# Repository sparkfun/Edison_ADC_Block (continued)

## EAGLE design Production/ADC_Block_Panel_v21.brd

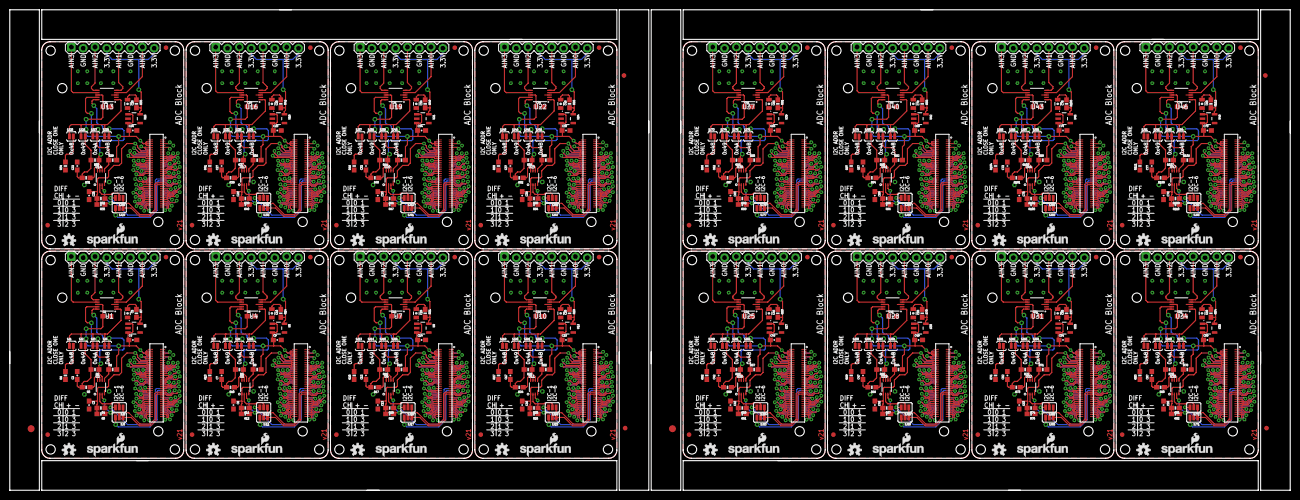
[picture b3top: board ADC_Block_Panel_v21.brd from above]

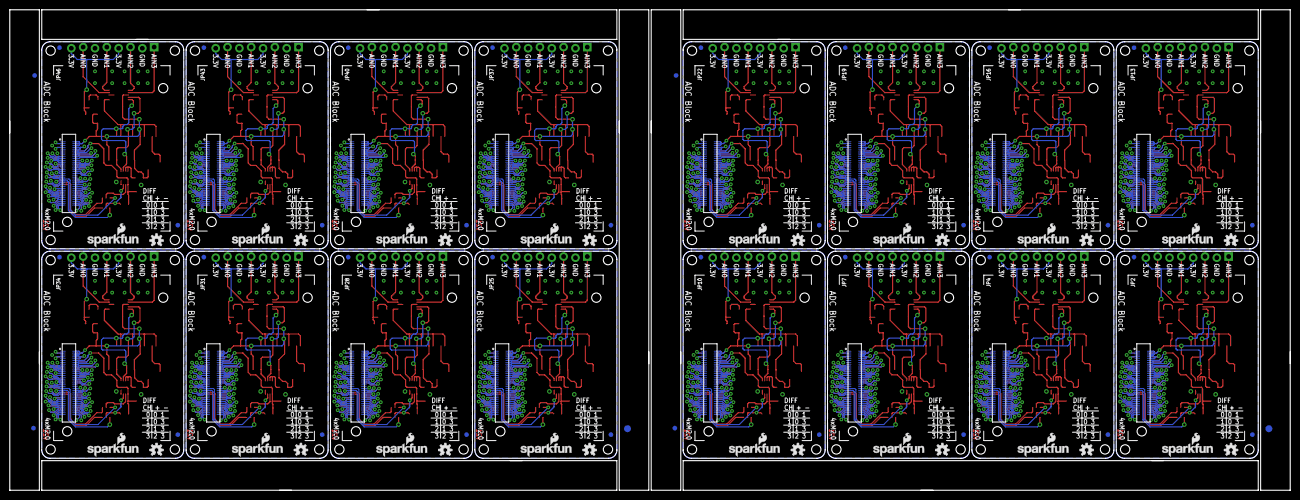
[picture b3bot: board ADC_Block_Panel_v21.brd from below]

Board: 2 copper layers, 274.8 x 103.1 mm, 524 parts (102 on the bottom side), 1136 nets.

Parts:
C1, C2, C3, C4, C6, C7, C8, C9, C11, C12, C13, C14, C16, C17, C18, C19, C21, C22, C23, C24, C26, C27, C28, C29, C31, C32, C33, C34, C36, C37, C38, C39, C41, C42, C43, C44, C46, C47, C48, C49, C51, C52, C53, C54, C56, C57, C58, C59, C61, C62, C63, C64, C66, C67, C68, C69, C71, C72, C73, C74, C76, C77, C78, C79: 0.1uF; 0603-CAP
C5, C10, C15, C20, C25, C30, C35, C40, C45, C50, C55, C60, C65, C70, C75, C80: 10uF; 0805-CAP
E$1, E$4, E$5, E$9: FIDUCIAL-1.5X3
E$2, E$3, E$6, E$7, E$8, E$10, E$11, E$12: FIDUCIAL-1X2
FID1, FID2, FID3, FID4, FID5, FID6, FID7, FID8, FID9, FID10, FID11, FID12, FID13, FID14, FID15, FID16, FID17, FID18, FID19, FID20, FID21, FID22, FID23, FID24, FID25, FID26, FID27, FID28, FID29, FID30, FID31, FID32, FID33, FID34, FID35, FID36, FID37, FID38, FID39, FID40, FID41, FID42, FID43, FID44, FID45, FID46, FID47, FID48, FID49, FID50, FID51, FID52, FID53, FID54, FID55, FID56, FID57, FID58, FID59, FID60, FID61, FID62, FID63, FID64: FIDUCIAL1X2; FIDUCIAL-1X2
JP1, JP6, JP9, JP12, JP15, JP18, JP21, JP24, JP27, JP30, JP33, JP36, JP39, JP42, JP45, JP48: 1X08_LOCK
JP2, JP4, JP7, JP10, JP13, JP16, JP19, JP22, JP25, JP28, JP31, JP34, JP37, JP40, JP43, JP46: EDISON_CONNECTOR_FULLMOUNTING_HOLES; EDISON_DAUGHTER
JP3, JP5, JP8, JP11, JP14, JP17, JP20, JP23, JP26, JP29, JP32, JP35, JP38, JP41, JP44, JP47: EDISON_CONNECTOR_FULLHEADER; DF40C-70DP-0.4(51)
LOGO1, LOGO3, LOGO6, LOGO7, LOGO10, LOGO11, LOGO14, LOGO15, LOGO18, LOGO19, LOGO22, LOGO23, LOGO26, LOGO27, LOGO30, LOGO31, LOGO34, LOGO35, LOGO38, LOGO39, LOGO42, LOGO43, LOGO46, LOGO47, LOGO50, LOGO51, LOGO54, LOGO55, LOGO58, LOGO59, LOGO62, LOGO63: SFE_LOGO_NAME_FLAME.1_INCH; SFE_LOGO_NAME_FLAME_.1
LOGO2, LOGO4, LOGO5, LOGO8, LOGO9, LOGO12, LOGO13, LOGO16, LOGO17, LOGO20, LOGO21, LOGO24, LOGO25, LOGO28, LOGO29, LOGO32, LOGO33, LOGO36, LOGO37, LOGO40, LOGO41, LOGO44, LOGO45, LOGO48, LOGO49, LOGO52, LOGO53, LOGO56, LOGO57, LOGO60, LOGO61, LOGO64: OSHW-LOGOS; OSHW-LOGO-S
R1, R2, R8, R9, R15, R16, R22, R23, R29, R30, R36, R37, R43, R44, R50, R51, R57, R58, R64, R65, R71, R72, R78, R79, R85, R86, R92, R93, R99, R100, R106, R107: 10K; 0603-RES
R3, R10, R17, R24, R31, R38, R45, R52, R59, R66, R73, R80, R87, R94, R101, R108: 200k; 0603-RES
R4, R5, R11, R12, R18, R19, R25, R26, R32, R33, R39, R40, R46, R47, R53, R54, R60, R61, R67, R68, R74, R75, R81, R82, R88, R89, R95, R96, R102, R103, R109, R110: DNP; 0603-RES
R6, R13, R20, R27, R34, R41, R48, R55, R62, R69, R76, R83, R90, R97, R104, R111: 2.2k; 0603-RES
R7, R14, R21, R28, R35, R42, R49, R56, R63, R70, R77, R84, R91, R98, R105, R112: 0.27; 0603-RES
SJ1, SJ7, SJ13, SJ19, SJ25, SJ31, SJ37, SJ43, SJ49, SJ55, SJ61, SJ67, SJ73, SJ79, SJ85, SJ91: JUMPER-PAD-2-NC_BY_PASTE; PAD-JUMPER-2-NC_BY_PASTE_YES_SILK
SJ2, SJ3, SJ4, SJ8, SJ9, SJ10, SJ14, SJ15, SJ16, SJ20, SJ21, SJ22, SJ26, SJ27, SJ28, SJ32, SJ33, SJ34, SJ38, SJ39, SJ40, SJ44, SJ45, SJ46, SJ50, SJ51, SJ52, SJ56, SJ57, SJ58, SJ62, SJ63, SJ64, SJ68, SJ69, SJ70, SJ74, SJ75, SJ76, SJ80, SJ81, SJ82, SJ86, SJ87, SJ88, SJ92, SJ93, SJ94: JUMPER-PAD-2-NOYES_SILK; PAD-JUMPER-2-NO_YES_SILK
SJ5, SJ11, SJ17, SJ23, SJ29, SJ35, SJ41, SJ47, SJ53, SJ59, SJ65, SJ71, SJ77, SJ83, SJ89, SJ95: SDA_SEL; PAD-JUMPER-3-2OF3_NC_BY_PASTE_YES_SILK_FULL_BOX
SJ6, SJ12, SJ18, SJ24, SJ30, SJ36, SJ42, SJ48, SJ54, SJ60, SJ66, SJ72, SJ78, SJ84, SJ90, SJ96: SCL_SEL; PAD-JUMPER-3-2OF3_NC_BY_PASTE_YES_SILK_FULL_BOX
U1, U4, U7, U10, U13, U16, U19, U22, U25, U28, U31, U34, U37, U40, U43, U46: ADS1015; MSOP10
U2, U5, U8, U11, U14, U17, U20, U23, U26, U29, U32, U35, U38, U41, U44, U47: PCA9306; PCA9306DC-1:1
U3, U6, U9, U12, U15, U18, U21, U24, U27, U30, U33, U36, U39, U42, U45, U48: 3.3V; SOT23-5

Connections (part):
1.8V: C3.1, JP2.12, JP3.12, R4.2, R5.2, U2.1
1.8V1: C8.1, JP4.12, JP5.12, R11.2, R12.2, U5.1
1.8V2: C13.1, JP7.12, JP8.12, R18.2, R19.2, U8.1
1.8V3: C18.1, JP10.12, JP11.12, R25.2, R26.2, U11.1
1.8V4: C23.1, JP13.12, JP14.12, R32.2, R33.2, U14.1
1.8V5: C28.1, JP16.12, JP17.12, R39.2, R40.2, U17.1
1.8V6: C33.1, JP19.12, JP20.12, R46.2, R47.2, U20.1
1.8V7: C38.1, JP22.12, JP23.12, R53.2, R54.2, U23.1
1.8V8: C43.1, JP25.12, JP26.12, R60.2, R61.2, U26.1
1.8V9: C48.1, JP28.12, JP29.12, R67.2, R68.2, U29.1
1.8V10: C53.1, JP31.12, JP32.12, R74.2, R75.2, U32.1
1.8V11: C58.1, JP34.12, JP35.12, R81.2, R82.2, U35.1
1.8V12: C63.1, JP37.12, JP38.12, R88.2, R89.2, U38.1
1.8V13: C68.1, JP40.12, JP41.12, R95.2, R96.2, U41.1
1.8V14: C73.1, JP43.12, JP44.12, R102.2, R103.2, U44.1
1.8V15: C78.1, JP46.12, JP47.12, R109.2, R110.2, U47.1
3.3V: JP2.8, JP2.10, JP3.8, JP3.10
3.3V1: JP4.8, JP4.10, JP5.8, JP5.10
3.3V2: JP7.8, JP7.10, JP8.8, JP8.10
3.3V3: JP10.8, JP10.10, JP11.8, JP11.10
3.3V4: JP13.8, JP13.10, JP14.8, JP14.10
3.3V5: JP16.8, JP16.10, JP17.8, JP17.10
3.3V6: JP19.8, JP19.10, JP20.8, JP20.10
3.3V7: JP22.8, JP22.10, JP23.8, JP23.10
3.3V8: JP25.8, JP25.10, JP26.8, JP26.10
3.3V9: JP28.8, JP28.10, JP29.8, JP29.10
3.3V10: JP31.8, JP31.10, JP32.8, JP32.10
3.3V11: JP34.8, JP34.10, JP35.8, JP35.10
3.3V12: JP37.8, JP37.10, JP38.8, JP38.10
3.3V13: JP40.8, JP40.10, JP41.8, JP41.10
3.3V14: JP43.8, JP43.10, JP44.8, JP44.10
3.3V15: JP46.8, JP46.10, JP47.8, JP47.10
A0+/AIN0: JP1.7, U1.4
A0+/AIN1: JP6.7, U4.4
A0+/AIN2: JP9.7, U7.4
A0+/AIN3: JP12.7, U10.4
A0+/AIN4: JP15.7, U13.4
A0+/AIN5: JP18.7, U16.4
A0+/AIN6: JP21.7, U19.4
A0+/AIN7: JP24.7, U22.4
A0+/AIN8: JP27.7, U25.4
A0+/AIN9: JP30.7, U28.4
A0+/AIN10: JP33.7, U31.4
A0+/AIN11: JP36.7, U34.4
A0+/AIN12: JP39.7, U37.4
A0+/AIN13: JP42.7, U40.4
A0+/AIN14: JP45.7, U43.4
A0+/AIN15: JP48.7, U46.4
A0-/AIN1: JP1.5, U1.5
A0-/AIN2: JP6.5, U4.5
A0-/AIN3: JP9.5, U7.5
A0-/AIN4: JP12.5, U10.5
A0-/AIN5: JP15.5, U13.5
A0-/AIN6: JP18.5, U16.5
A0-/AIN7: JP21.5, U19.5
A0-/AIN8: JP24.5, U22.5
A0-/AIN9: JP27.5, U25.5
A0-/AIN10: JP30.5, U28.5
A0-/AIN11: JP33.5, U31.5
A0-/AIN12: JP36.5, U34.5
A0-/AIN13: JP39.5, U37.5
A0-/AIN14: JP42.5, U40.5
A0-/AIN15: JP45.5, U43.5
A0-/AIN16: JP48.5, U46.5
A1+/AIN1: JP6.3, U4.6
A1+/AIN2: JP1.3, U1.6
A1+/AIN3: JP9.3, U7.6
A1+/AIN4: JP12.3, U10.6
A1+/AIN5: JP15.3, U13.6
A1+/AIN6: JP18.3, U16.6
A1+/AIN7: JP21.3, U19.6
A1+/AIN8: JP24.3, U22.6
A1+/AIN9: JP27.3, U25.6
A1+/AIN10: JP30.3, U28.6
A1+/AIN11: JP33.3, U31.6
A1+/AIN12: JP36.3, U34.6
A1+/AIN13: JP39.3, U37.6
A1+/AIN14: JP42.3, U40.6
A1+/AIN15: JP45.3, U43.6
A1+/AIN16: JP48.3, U46.6
A1-/AIN1: JP6.1, U4.7
A1-/AIN2: JP9.1, U7.7
A1-/AIN3: JP1.1, U1.7
A1-/AIN4: JP12.1, U10.7
A1-/AIN5: JP15.1, U13.7
A1-/AIN6: JP18.1, U16.7
A1-/AIN7: JP21.1, U19.7
A1-/AIN8: JP24.1, U22.7
A1-/AIN9: JP27.1, U25.7
A1-/AIN10: JP30.1, U28.7
A1-/AIN11: JP33.1, U31.7
A1-/AIN12: JP36.1, U34.7
A1-/AIN13: JP39.1, U37.7
A1-/AIN14: JP42.1, U40.7
A1-/AIN15: JP45.1, U43.7
A1-/AIN16: JP48.1, U46.7
ADDR: SJ1.1, SJ2.1, SJ3.1, SJ4.1, U1.1
ADDR1: SJ7.1, SJ8.1, SJ9.1, SJ10.1, U4.1
ADDR2: SJ13.1, SJ14.1, SJ15.1, SJ16.1, U7.1
ADDR3: SJ19.1, SJ20.1, SJ21.1, SJ22.1, U10.1
ADDR4: SJ25.1, SJ26.1, SJ27.1, SJ28.1, U13.1
ADDR5: SJ31.1, SJ32.1, SJ33.1, SJ34.1, U16.1
ADDR6: SJ37.1, SJ38.1, SJ39.1, SJ40.1, U19.1
ADDR7: SJ43.1, SJ44.1, SJ45.1, SJ46.1, U22.1
ADDR8: SJ49.1, SJ50.1, SJ51.1, SJ52.1, U25.1
ADDR9: SJ55.1, SJ56.1, SJ57.1, SJ58.1, U28.1
ADDR10: SJ61.1, SJ62.1, SJ63.1, SJ64.1, U31.1
ADDR11: SJ67.1, SJ68.1, SJ69.1, SJ70.1, U34.1
ADDR12: SJ73.1, SJ74.1, SJ75.1, SJ76.1, U37.1
ADDR13: SJ79.1, SJ80.1, SJ81.1, SJ82.1, U40.1
ADDR14: SJ85.1, SJ86.1, SJ87.1, SJ88.1, U43.1
ADDR15: SJ91.1, SJ92.1, SJ93.1, SJ94.1, U46.1
DCIN: JP2.14, JP3.14
DCIN1: JP4.14, JP5.14
DCIN2: JP7.14, JP8.14
DCIN3: JP10.14, JP11.14
DCIN4: JP13.14, JP14.14
DCIN5: JP16.14, JP17.14
DCIN6: JP19.14, JP20.14
DCIN7: JP22.14, JP23.14
DCIN8: JP25.14, JP26.14
DCIN9: JP28.14, JP29.14
DCIN10: JP31.14, JP32.14
DCIN11: JP34.14, JP35.14
DCIN12: JP37.14, JP38.14
DCIN13: JP40.14, JP41.14
DCIN14: JP43.14, JP44.14
DCIN15: JP46.14, JP47.14
FAULT: JP2.19, JP3.19
FAULT1: JP4.19, JP5.19
FAULT2: JP7.19, JP8.19
FAULT3: JP10.19, JP11.19
FAULT4: JP13.19, JP14.19
FAULT5: JP16.19, JP17.19
FAULT6: JP19.19, JP20.19
FAULT7: JP22.19, JP23.19
FAULT8: JP25.19, JP26.19
FAULT9: JP28.19, JP29.19
FAULT10: JP31.19, JP32.19
FAULT11: JP34.19, JP35.19
FAULT12: JP37.19, JP38.19
FAULT13: JP40.19, JP41.19
FAULT14: JP43.19, JP44.19
FAULT15: JP46.19, JP47.19
FW_RCVR: JP2.69, JP3.69
FW_RCVR1: JP4.69, JP5.69
FW_RCVR2: JP7.69, JP8.69
FW_RCVR3: JP10.69, JP11.69
FW_RCVR4: JP13.69, JP14.69
FW_RCVR5: JP16.69, JP17.69
FW_RCVR6: JP19.69, JP20.69
FW_RCVR7: JP22.69, JP23.69
FW_RCVR8: JP25.69, JP26.69
FW_RCVR9: JP28.69, JP29.69
FW_RCVR10: JP31.69, JP32.69
FW_RCVR11: JP34.69, JP35.69
FW_RCVR12: JP37.69, JP38.69
FW_RCVR13: JP40.69, JP41.69
FW_RCVR14: JP43.69, JP44.69
FW_RCVR15: JP46.69, JP47.69
GND: C1.2, C2.2, C3.2, C4.2, C5.2, JP1.2, JP1.6, JP2.1, JP2.5, JP2.9, JP2.11, JP2.13, JP2.15, JP3.1, JP3.5, JP3.9, JP3.11, JP3.13, JP3.15, R6.1, U1.3, U2.4, U3.2
GND1: C6.2, C7.2, C8.2, C9.2, C10.2, JP4.1, JP4.5, JP4.9, JP4.11, JP4.13, JP4.15, JP5.1, JP5.5, JP5.9, JP5.11, JP5.13, JP5.15, JP6.2, JP6.6, R13.1, U4.3, U5.4, U6.2
GND2: C11.2, C12.2, C13.2, C14.2, C15.2, JP7.1, JP7.5, JP7.9, JP7.11, JP7.13, JP7.15, JP8.1, JP8.5, JP8.9, JP8.11, JP8.13, JP8.15, JP9.2, JP9.6, R20.1, U7.3, U8.4, U9.2
GND3: C16.2, C17.2, C18.2, C19.2, C20.2, JP10.1, JP10.5, JP10.9, JP10.11, JP10.13, JP10.15, JP11.1, JP11.5, JP11.9, JP11.11, JP11.13, JP11.15, JP12.2, JP12.6, R27.1, U10.3, U11.4, U12.2
GND4: C21.2, C22.2, C23.2, C24.2, C25.2, JP13.1, JP13.5, JP13.9, JP13.11, JP13.13, JP13.15, JP14.1, JP14.5, JP14.9, JP14.11, JP14.13, JP14.15, JP15.2, JP15.6, R34.1, U13.3, U14.4, U15.2
GND5: C26.2, C27.2, C28.2, C29.2, C30.2, JP16.1, JP16.5, JP16.9, JP16.11, JP16.13, JP16.15, JP17.1, JP17.5, JP17.9, JP17.11, JP17.13, JP17.15, JP18.2, JP18.6, R41.1, U16.3, U17.4, U18.2
GND6: C31.2, C32.2, C33.2, C34.2, C35.2, JP19.1, JP19.5, JP19.9, JP19.11, JP19.13, JP19.15, JP20.1, JP20.5, JP20.9, JP20.11, JP20.13, JP20.15, JP21.2, JP21.6, R48.1, U19.3, U20.4, U21.2
GND7: C36.2, C37.2, C38.2, C39.2, C40.2, JP22.1, JP22.5, JP22.9, JP22.11, JP22.13, JP22.15, JP23.1, JP23.5, JP23.9, JP23.11, JP23.13, JP23.15, JP24.2, JP24.6, R55.1, U22.3, U23.4, U24.2
GND8: C41.2, C42.2, C43.2, C44.2, C45.2, JP25.1, JP25.5, JP25.9, JP25.11, JP25.13, JP25.15, JP26.1, JP26.5, JP26.9, JP26.11, JP26.13, JP26.15, JP27.2, JP27.6, R62.1, U25.3, U26.4, U27.2
GND9: C46.2, C47.2, C48.2, C49.2, C50.2, JP28.1, JP28.5, JP28.9, JP28.11, JP28.13, JP28.15, JP29.1, JP29.5, JP29.9, JP29.11, JP29.13, JP29.15, JP30.2, JP30.6, R69.1, U28.3, U29.4, U30.2
GND10: C51.2, C52.2, C53.2, C54.2, C55.2, JP31.1, JP31.5, JP31.9, JP31.11, JP31.13, JP31.15, JP32.1, JP32.5, JP32.9, JP32.11, JP32.13, JP32.15, JP33.2, JP33.6, R76.1, U31.3, U32.4, U33.2
GND11: C56.2, C57.2, C58.2, C59.2, C60.2, JP34.1, JP34.5, JP34.9, JP34.11, JP34.13, JP34.15, JP35.1, JP35.5, JP35.9, JP35.11, JP35.13, JP35.15, JP36.2, JP36.6, R83.1, U34.3, U35.4, U36.2
GND12: C61.2, C62.2, C63.2, C64.2, C65.2, JP37.1, JP37.5, JP37.9, JP37.11, JP37.13, JP37.15, JP38.1, JP38.5, JP38.9, JP38.11, JP38.13, JP38.15, JP39.2, JP39.6, R90.1, U37.3, U38.4, U39.2
GND13: C66.2, C67.2, C68.2, C69.2, C70.2, JP40.1, JP40.5, JP40.9, JP40.11, JP40.13, JP40.15, JP41.1, JP41.5, JP41.9, JP41.11, JP41.13, JP41.15, JP42.2, JP42.6, R97.1, U40.3, U41.4, U42.2
GND14: C71.2, C72.2, C73.2, C74.2, C75.2, JP43.1, JP43.5, JP43.9, JP43.11, JP43.13, JP43.15, JP44.1, JP44.5, JP44.9, JP44.11, JP44.13, JP44.15, JP45.2, JP45.6, R104.1, U43.3, U44.4, U45.2
GND15: C76.2, C77.2, C78.2, C79.2, C80.2, JP46.1, JP46.5, JP46.9, JP46.11, JP46.13, JP46.15, JP47.1, JP47.5, JP47.9, JP47.11, JP47.13, JP47.15, JP48.2, JP48.6, R111.1, U46.3, U47.4, U48.2
GP1: JP4.48, JP5.48
GP2: JP4.42, JP5.42
GP3: JP4.34, JP5.34
GP4: JP4.32, JP5.32
GP5: JP4.30, JP5.30
GP6: JP4.28, JP5.28
GP7: JP4.26, JP5.26
GP8: JP4.25, JP5.25
GP9: JP4.24, JP5.24
GP10: JP7.48, JP8.48
GP11: JP7.42, JP8.42
GP12: JP7.34, JP8.34
GP12_PWM0: JP2.35, JP3.35
GP12_PWM1: JP4.35, JP5.35
GP12_PWM2: JP7.35, JP8.35
GP12_PWM3: JP10.35, JP11.35
GP12_PWM4: JP13.35, JP14.35
GP12_PWM5: JP16.35, JP17.35
GP12_PWM6: JP19.35, JP20.35
GP12_PWM7: JP22.35, JP23.35
GP12_PWM8: JP25.35, JP26.35
GP12_PWM9: JP28.35, JP29.35
GP12_PWM10: JP31.35, JP32.35
GP12_PWM11: JP34.35, JP35.35
GP12_PWM12: JP37.35, JP38.35
GP12_PWM13: JP40.35, JP41.35
GP12_PWM14: JP43.35, JP44.35
GP12_PWM15: JP46.35, JP47.35
GP13: JP7.32, JP8.32
GP13_PWM1: JP2.33, JP3.33
GP13_PWM2: JP4.33, JP5.33
GP13_PWM3: JP7.33, JP8.33
GP13_PWM4: JP10.33, JP11.33
GP13_PWM5: JP13.33, JP14.33
GP13_PWM6: JP16.33, JP17.33
GP13_PWM7: JP19.33, JP20.33
GP13_PWM8: JP22.33, JP23.33
GP13_PWM9: JP25.33, JP26.33
GP13_PWM10: JP28.33, JP29.33
GP13_PWM11: JP31.33, JP32.33
GP13_PWM12: JP34.33, JP35.33
GP13_PWM13: JP37.33, JP38.33
GP13_PWM14: JP40.33, JP41.33
GP13_PWM15: JP43.33, JP44.33
GP13_PWM16: JP46.33, JP47.33
GP14: JP2.48, JP3.48
GP15: JP2.42, JP3.42
GP16: JP7.30, JP8.30
GP17: JP7.28, JP8.28
GP18: JP7.26, JP8.26
GP19: JP7.25, JP8.25
GP19_I2C_1_SCL: JP2.41, JP3.41, SJ6.3
GP19_I2C_1_SCL1: JP4.41, JP5.41, SJ12.3
GP19_I2C_1_SCL2: JP7.41, JP8.41, SJ18.3
GP19_I2C_1_SCL3: JP10.41, JP11.41, SJ24.3
GP19_I2C_1_SCL4: JP13.41, JP14.41, SJ30.3
GP19_I2C_1_SCL5: JP16.41, JP17.41, SJ36.3
GP19_I2C_1_SCL6: JP19.41, JP20.41, SJ42.3
GP19_I2C_1_SCL7: JP22.41, JP23.41, SJ48.3
GP19_I2C_1_SCL8: JP25.41, JP26.41, SJ54.3
GP19_I2C_1_SCL9: JP28.41, JP29.41, SJ60.3
GP19_I2C_1_SCL10: JP31.41, JP32.41, SJ66.3
GP19_I2C_1_SCL11: JP34.41, JP35.41, SJ72.3
GP19_I2C_1_SCL12: JP37.41, JP38.41, SJ78.3
GP19_I2C_1_SCL13: JP40.41, JP41.41, SJ84.3
GP19_I2C_1_SCL14: JP43.41, JP44.41, SJ90.3
GP19_I2C_1_SCL15: JP46.41, JP47.41, SJ96.3
GP20: JP7.24, JP8.24
GP20_I2C_1_SDA: JP2.43, JP3.43, SJ5.3
GP20_I2C_1_SDA1: JP4.43, JP5.43, SJ11.3
GP20_I2C_1_SDA2: JP7.43, JP8.43, SJ17.3
GP20_I2C_1_SDA3: JP10.43, JP11.43, SJ23.3
GP20_I2C_1_SDA4: JP13.43, JP14.43, SJ29.3
GP20_I2C_1_SDA5: JP16.43, JP17.43, SJ35.3
GP20_I2C_1_SDA6: JP19.43, JP20.43, SJ41.3
GP20_I2C_1_SDA7: JP22.43, JP23.43, SJ47.3
GP20_I2C_1_SDA8: JP25.43, JP26.43, SJ53.3
GP20_I2C_1_SDA9: JP28.43, JP29.43, SJ59.3
GP20_I2C_1_SDA10: JP31.43, JP32.43, SJ65.3
GP20_I2C_1_SDA11: JP34.43, JP35.43, SJ71.3
GP20_I2C_1_SDA12: JP37.43, JP38.43, SJ77.3
GP20_I2C_1_SDA13: JP40.43, JP41.43, SJ83.3
GP20_I2C_1_SDA14: JP43.43, JP44.43, SJ89.3
GP20_I2C_1_SDA15: JP46.43, JP47.43, SJ95.3
GP21: JP10.48, JP11.48
GP22: JP10.42, JP11.42
GP23: JP10.34, JP11.34
GP24: JP10.32, JP11.32
GP25: JP10.30, JP11.30
GP26: JP10.28, JP11.28
GP27: JP10.26, JP11.26
GP27_I2C_6_SCL: JP2.45, JP3.45, SJ6.1
GP27_I2C_6_SCL1: JP4.45, JP5.45, SJ12.1
GP27_I2C_6_SCL2: JP7.45, JP8.45, SJ18.1
GP27_I2C_6_SCL3: JP10.45, JP11.45, SJ24.1
GP27_I2C_6_SCL4: JP13.45, JP14.45, SJ30.1
GP27_I2C_6_SCL5: JP16.45, JP17.45, SJ36.1
GP27_I2C_6_SCL6: JP19.45, JP20.45, SJ42.1
GP27_I2C_6_SCL7: JP22.45, JP23.45, SJ48.1
GP27_I2C_6_SCL8: JP25.45, JP26.45, SJ54.1
GP27_I2C_6_SCL9: JP28.45, JP29.45, SJ60.1
GP27_I2C_6_SCL10: JP31.45, JP32.45, SJ66.1
GP27_I2C_6_SCL11: JP34.45, JP35.45, SJ72.1
GP27_I2C_6_SCL12: JP37.45, JP38.45, SJ78.1
GP27_I2C_6_SCL13: JP40.45, JP41.45, SJ84.1
GP27_I2C_6_SCL14: JP43.45, JP44.45, SJ90.1
GP27_I2C_6_SCL15: JP46.45, JP47.45, SJ96.1
GP28: JP10.25, JP11.25
GP28_I2C_6_SDA: JP2.47, JP3.47, SJ5.1
GP28_I2C_6_SDA1: JP4.47, JP5.47, SJ11.1
GP28_I2C_6_SDA2: JP7.47, JP8.47, SJ17.1
GP28_I2C_6_SDA3: JP10.47, JP11.47, SJ23.1
GP28_I2C_6_SDA4: JP13.47, JP14.47, SJ29.1
GP28_I2C_6_SDA5: JP16.47, JP17.47, SJ35.1
GP28_I2C_6_SDA6: JP19.47, JP20.47, SJ41.1
GP28_I2C_6_SDA7: JP22.47, JP23.47, SJ47.1
GP28_I2C_6_SDA8: JP25.47, JP26.47, SJ53.1
GP28_I2C_6_SDA9: JP28.47, JP29.47, SJ59.1
GP28_I2C_6_SDA10: JP31.47, JP32.47, SJ65.1
GP28_I2C_6_SDA11: JP34.47, JP35.47, SJ71.1
GP28_I2C_6_SDA12: JP37.47, JP38.47, SJ77.1
GP28_I2C_6_SDA13: JP40.47, JP41.47, SJ83.1
GP28_I2C_6_SDA14: JP43.47, JP44.47, SJ89.1
GP28_I2C_6_SDA15: JP46.47, JP47.47, SJ95.1
GP29: JP10.24, JP11.24
GP30: JP13.48, JP14.48
GP31: JP13.42, JP14.42
GP32: JP13.34, JP14.34
GP33: JP13.32, JP14.32
GP34: JP13.30, JP14.30
GP35: JP13.28, JP14.28
GP36: JP13.26, JP14.26
GP37: JP13.25, JP14.25
GP38: JP13.24, JP14.24
GP39: JP16.48, JP17.48
GP40: JP16.42, JP17.42
GP40_I2S_2_CLK: JP2.52, JP3.52
GP40_I2S_2_CLK1: JP4.52, JP5.52
GP40_I2S_2_CLK2: JP7.52, JP8.52
GP40_I2S_2_CLK3: JP10.52, JP11.52
GP40_I2S_2_CLK4: JP13.52, JP14.52
GP40_I2S_2_CLK5: JP16.52, JP17.52
GP40_I2S_2_CLK6: JP19.52, JP20.52
GP40_I2S_2_CLK7: JP22.52, JP23.52
GP40_I2S_2_CLK8: JP25.52, JP26.52
GP40_I2S_2_CLK9: JP28.52, JP29.52
GP40_I2S_2_CLK10: JP31.52, JP32.52
GP40_I2S_2_CLK11: JP34.52, JP35.52
GP40_I2S_2_CLK12: JP37.52, JP38.52
GP40_I2S_2_CLK13: JP40.52, JP41.52
GP40_I2S_2_CLK14: JP43.52, JP44.52
GP40_I2S_2_CLK15: JP46.52, JP47.52
GP41: JP16.34, JP17.34
GP41_I2S_2_FS: JP2.54, JP3.54
GP41_I2S_2_FS1: JP4.54, JP5.54
GP41_I2S_2_FS2: JP7.54, JP8.54
GP41_I2S_2_FS3: JP10.54, JP11.54
GP41_I2S_2_FS4: JP13.54, JP14.54
GP41_I2S_2_FS5: JP16.54, JP17.54
GP41_I2S_2_FS6: JP19.54, JP20.54
GP41_I2S_2_FS7: JP22.54, JP23.54
GP41_I2S_2_FS8: JP25.54, JP26.54
GP41_I2S_2_FS9: JP28.54, JP29.54
GP41_I2S_2_FS10: JP31.54, JP32.54
GP41_I2S_2_FS11: JP34.54, JP35.54
GP41_I2S_2_FS12: JP37.54, JP38.54
GP41_I2S_2_FS13: JP40.54, JP41.54
GP41_I2S_2_FS14: JP43.54, JP44.54
GP41_I2S_2_FS15: JP46.54, JP47.54
GP42: JP16.32, JP17.32
GP42_I2S_2_RXD: JP2.50, JP3.50
GP42_I2S_2_RXD1: JP4.50, JP5.50
GP42_I2S_2_RXD2: JP7.50, JP8.50
GP42_I2S_2_RXD3: JP10.50, JP11.50
GP42_I2S_2_RXD4: JP13.50, JP14.50
GP42_I2S_2_RXD5: JP16.50, JP17.50
GP42_I2S_2_RXD6: JP19.50, JP20.50
GP42_I2S_2_RXD7: JP22.50, JP23.50
GP42_I2S_2_RXD8: JP25.50, JP26.50
GP42_I2S_2_RXD9: JP28.50, JP29.50
GP42_I2S_2_RXD10: JP31.50, JP32.50
GP42_I2S_2_RXD11: JP34.50, JP35.50
GP42_I2S_2_RXD12: JP37.50, JP38.50
GP42_I2S_2_RXD13: JP40.50, JP41.50
GP42_I2S_2_RXD14: JP43.50, JP44.50
GP42_I2S_2_RXD15: JP46.50, JP47.50
GP43: JP16.30, JP17.30
GP43_I2S_2_TXD: JP2.56, JP3.56
GP43_I2S_2_TXD1: JP4.56, JP5.56
GP43_I2S_2_TXD2: JP7.56, JP8.56
GP43_I2S_2_TXD3: JP10.56, JP11.56
GP43_I2S_2_TXD4: JP13.56, JP14.56
GP43_I2S_2_TXD5: JP16.56, JP17.56
GP43_I2S_2_TXD6: JP19.56, JP20.56
GP43_I2S_2_TXD7: JP22.56, JP23.56
GP43_I2S_2_TXD8: JP25.56, JP26.56
GP43_I2S_2_TXD9: JP28.56, JP29.56
GP43_I2S_2_TXD10: JP31.56, JP32.56
GP43_I2S_2_TXD11: JP34.56, JP35.56
GP43_I2S_2_TXD12: JP37.56, JP38.56
GP43_I2S_2_TXD13: JP40.56, JP41.56
GP43_I2S_2_TXD14: JP43.56, JP44.56
GP43_I2S_2_TXD15: JP46.56, JP47.56
GP44: JP2.24, JP3.24
GP45: JP2.26, JP3.26
GP46: JP2.28, JP3.28
GP47: JP2.30, JP3.30
GP48: JP2.32, JP3.32
GP49: JP2.34, JP3.34
GP50: JP16.28, JP17.28
GP51: JP16.26, JP17.26
GP52: JP16.25, JP17.25
GP53: JP16.24, JP17.24
GP54: JP19.48, JP20.48
GP55: JP19.42, JP20.42
GP56: JP19.34, JP20.34
GP57: JP19.32, JP20.32
GP58: JP19.30, JP20.30
GP59: JP19.28, JP20.28
GP60: JP19.26, JP20.26
GP61: JP19.25, JP20.25
GP62: JP19.24, JP20.24
GP63: JP22.48, JP23.48
GP64: JP22.42, JP23.42
GP65: JP22.34, JP23.34
GP66: JP22.32, JP23.32
GP67: JP22.30, JP23.30
GP68: JP22.28, JP23.28
GP69: JP22.26, JP23.26
GP70: JP22.25, JP23.25
GP71: JP22.24, JP23.24
GP72: JP25.48, JP26.48
GP73: JP25.42, JP26.42
GP74: JP25.34, JP26.34
GP75: JP25.32, JP26.32
GP76: JP25.30, JP26.30
GP77: JP25.28, JP26.28
GP77_SD_0_CD#: JP2.60, JP3.60
GP77_SD_0_CD#1: JP4.60, JP5.60
GP77_SD_0_CD#2: JP7.60, JP8.60
GP77_SD_0_CD#3: JP10.60, JP11.60
GP77_SD_0_CD#4: JP13.60, JP14.60
GP77_SD_0_CD#5: JP16.60, JP17.60
GP77_SD_0_CD#6: JP19.60, JP20.60
GP77_SD_0_CD#7: JP22.60, JP23.60
GP77_SD_0_CD#8: JP25.60, JP26.60
GP77_SD_0_CD#9: JP28.60, JP29.60
GP77_SD_0_CD#10: JP31.60, JP32.60
GP77_SD_0_CD#11: JP34.60, JP35.60
GP77_SD_0_CD#12: JP37.60, JP38.60
GP77_SD_0_CD#13: JP40.60, JP41.60
GP77_SD_0_CD#14: JP43.60, JP44.60
GP77_SD_0_CD#15: JP46.60, JP47.60
GP78: JP25.26, JP26.26
GP78_SD_0_CLK: JP2.58, JP3.58
GP78_SD_0_CLK1: JP4.58, JP5.58
GP78_SD_0_CLK2: JP7.58, JP8.58
GP78_SD_0_CLK3: JP10.58, JP11.58
GP78_SD_0_CLK4: JP13.58, JP14.58
GP78_SD_0_CLK5: JP16.58, JP17.58
GP78_SD_0_CLK6: JP19.58, JP20.58
GP78_SD_0_CLK7: JP22.58, JP23.58
GP78_SD_0_CLK8: JP25.58, JP26.58
GP78_SD_0_CLK9: JP28.58, JP29.58
GP78_SD_0_CLK10: JP31.58, JP32.58
GP78_SD_0_CLK11: JP34.58, JP35.58
GP78_SD_0_CLK12: JP37.58, JP38.58
GP78_SD_0_CLK13: JP40.58, JP41.58
GP78_SD_0_CLK14: JP43.58, JP44.58
GP78_SD_0_CLK15: JP46.58, JP47.58
GP79: JP25.25, JP26.25
GP79_SD_0_CMD: JP2.62, JP3.62
GP79_SD_0_CMD1: JP4.62, JP5.62
GP79_SD_0_CMD2: JP7.62, JP8.62
GP79_SD_0_CMD3: JP10.62, JP11.62
GP79_SD_0_CMD4: JP13.62, JP14.62
GP79_SD_0_CMD5: JP16.62, JP17.62
GP79_SD_0_CMD6: JP19.62, JP20.62
GP79_SD_0_CMD7: JP22.62, JP23.62
GP79_SD_0_CMD8: JP25.62, JP26.62
GP79_SD_0_CMD9: JP28.62, JP29.62
GP79_SD_0_CMD10: JP31.62, JP32.62
GP79_SD_0_CMD11: JP34.62, JP35.62
GP79_SD_0_CMD12: JP37.62, JP38.62
GP79_SD_0_CMD13: JP40.62, JP41.62
GP79_SD_0_CMD14: JP43.62, JP44.62
GP79_SD_0_CMD15: JP46.62, JP47.62
GP80: JP25.24, JP26.24
GP80_SD_0_DAT0: JP2.66, JP3.66
GP80_SD_0_DAT1: JP4.66, JP5.66
GP80_SD_0_DAT2: JP7.66, JP8.66
GP80_SD_0_DAT3: JP10.66, JP11.66
GP80_SD_0_DAT4: JP13.66, JP14.66
GP80_SD_0_DAT5: JP16.66, JP17.66
GP80_SD_0_DAT6: JP19.66, JP20.66
GP80_SD_0_DAT7: JP22.66, JP23.66
GP80_SD_0_DAT8: JP25.66, JP26.66
GP80_SD_0_DAT9: JP28.66, JP29.66
GP80_SD_0_DAT10: JP31.66, JP32.66
GP80_SD_0_DAT11: JP34.66, JP35.66
GP80_SD_0_DAT12: JP37.66, JP38.66
GP80_SD_0_DAT13: JP40.66, JP41.66
GP80_SD_0_DAT14: JP43.66, JP44.66
GP80_SD_0_DAT15: JP46.66, JP47.66
GP81: JP28.48, JP29.48
GP81_SD_0_DAT1: JP2.70, JP3.70
GP81_SD_0_DAT2: JP4.70, JP5.70
GP81_SD_0_DAT3: JP7.70, JP8.70
GP81_SD_0_DAT4: JP10.70, JP11.70
GP81_SD_0_DAT5: JP13.70, JP14.70
GP81_SD_0_DAT6: JP16.70, JP17.70
GP81_SD_0_DAT7: JP19.70, JP20.70
GP81_SD_0_DAT8: JP22.70, JP23.70
GP81_SD_0_DAT9: JP25.70, JP26.70
GP81_SD_0_DAT10: JP28.70, JP29.70
GP81_SD_0_DAT11: JP31.70, JP32.70
GP81_SD_0_DAT12: JP34.70, JP35.70
GP81_SD_0_DAT13: JP37.70, JP38.70
GP81_SD_0_DAT14: JP40.70, JP41.70
GP81_SD_0_DAT15: JP43.70, JP44.70
GP81_SD_0_DAT16: JP46.70, JP47.70
GP82: JP28.42, JP29.42
GP82_SD_0_DAT1: JP4.64, JP5.64
GP82_SD_0_DAT2: JP2.64, JP3.64
GP82_SD_0_DAT3: JP7.64, JP8.64
GP82_SD_0_DAT4: JP10.64, JP11.64
GP82_SD_0_DAT5: JP13.64, JP14.64
GP82_SD_0_DAT6: JP16.64, JP17.64
GP82_SD_0_DAT7: JP19.64, JP20.64
GP82_SD_0_DAT8: JP22.64, JP23.64
GP82_SD_0_DAT9: JP25.64, JP26.64
GP82_SD_0_DAT10: JP28.64, JP29.64
GP82_SD_0_DAT11: JP31.64, JP32.64
GP82_SD_0_DAT12: JP34.64, JP35.64
GP82_SD_0_DAT13: JP37.64, JP38.64
GP82_SD_0_DAT14: JP40.64, JP41.64
GP82_SD_0_DAT15: JP43.64, JP44.64
GP82_SD_0_DAT16: JP46.64, JP47.64
GP83: JP28.34, JP29.34
GP83_SD_0_DAT1: JP4.68, JP5.68
GP83_SD_0_DAT2: JP7.68, JP8.68
GP83_SD_0_DAT3: JP2.68, JP3.68
GP83_SD_0_DAT4: JP10.68, JP11.68
GP83_SD_0_DAT5: JP13.68, JP14.68
GP83_SD_0_DAT6: JP16.68, JP17.68
GP83_SD_0_DAT7: JP19.68, JP20.68
GP83_SD_0_DAT8: JP22.68, JP23.68
GP83_SD_0_DAT9: JP25.68, JP26.68
GP83_SD_0_DAT10: JP28.68, JP29.68
GP83_SD_0_DAT11: JP31.68, JP32.68
GP83_SD_0_DAT12: JP34.68, JP35.68
GP83_SD_0_DAT13: JP37.68, JP38.68
GP83_SD_0_DAT14: JP40.68, JP41.68
GP83_SD_0_DAT15: JP43.68, JP44.68
GP83_SD_0_DAT16: JP46.68, JP47.68
GP84: JP28.32, JP29.32
GP84_SD_CLK_FB: JP2.44, JP3.44
GP84_SD_CLK_FB1: JP4.44, JP5.44
GP84_SD_CLK_FB2: JP7.44, JP8.44
GP84_SD_CLK_FB3: JP10.44, JP11.44
GP84_SD_CLK_FB4: JP13.44, JP14.44
GP84_SD_CLK_FB5: JP16.44, JP17.44
GP84_SD_CLK_FB6: JP19.44, JP20.44
GP84_SD_CLK_FB7: JP22.44, JP23.44
GP84_SD_CLK_FB8: JP25.44, JP26.44
GP84_SD_CLK_FB9: JP28.44, JP29.44
GP84_SD_CLK_FB10: JP31.44, JP32.44
GP84_SD_CLK_FB11: JP34.44, JP35.44
GP84_SD_CLK_FB12: JP37.44, JP38.44
GP84_SD_CLK_FB13: JP40.44, JP41.44
GP84_SD_CLK_FB14: JP43.44, JP44.44
GP84_SD_CLK_FB15: JP46.44, JP47.44
GP85: JP28.30, JP29.30
GP86: JP28.28, JP29.28
GP87: JP28.26, JP29.26
GP88: JP28.25, JP29.25
GP89: JP28.24, JP29.24
GP90: JP31.48, JP32.48
GP91: JP31.42, JP32.42
GP92: JP31.34, JP32.34
GP93: JP31.32, JP32.32
GP94: JP31.30, JP32.30
GP95: JP31.28, JP32.28
GP96: JP31.26, JP32.26
GP97: JP31.25, JP32.25
GP98: JP31.24, JP32.24
GP99: JP34.48, JP35.48
GP100: JP34.42, JP35.42
GP101: JP34.34, JP35.34
GP102: JP34.32, JP35.32
GP103: JP34.30, JP35.30
GP104: JP34.28, JP35.28
GP105: JP34.26, JP35.26
GP106: JP34.25, JP35.25
GP107: JP34.24, JP35.24
GP108: JP37.48, JP38.48
GP109: JP37.42, JP38.42
GP109_SPI_2_CLK: JP2.55, JP3.55
GP109_SPI_2_CLK1: JP4.55, JP5.55
GP109_SPI_2_CLK2: JP7.55, JP8.55
GP109_SPI_2_CLK3: JP10.55, JP11.55
GP109_SPI_2_CLK4: JP13.55, JP14.55
GP109_SPI_2_CLK5: JP16.55, JP17.55
GP109_SPI_2_CLK6: JP19.55, JP20.55
GP109_SPI_2_CLK7: JP22.55, JP23.55
GP109_SPI_2_CLK8: JP25.55, JP26.55
GP109_SPI_2_CLK9: JP28.55, JP29.55
GP109_SPI_2_CLK10: JP31.55, JP32.55
GP109_SPI_2_CLK11: JP34.55, JP35.55
GP109_SPI_2_CLK12: JP37.55, JP38.55
GP109_SPI_2_CLK13: JP40.55, JP41.55
GP109_SPI_2_CLK14: JP43.55, JP44.55
GP109_SPI_2_CLK15: JP46.55, JP47.55
GP110: JP37.34, JP38.34
GP110_SPI_2_FS0: JP2.53, JP3.53
GP110_SPI_2_FS1: JP4.53, JP5.53
GP110_SPI_2_FS2: JP7.53, JP8.53
GP110_SPI_2_FS3: JP10.53, JP11.53
GP110_SPI_2_FS4: JP13.53, JP14.53
GP110_SPI_2_FS5: JP16.53, JP17.53
GP110_SPI_2_FS6: JP19.53, JP20.53
GP110_SPI_2_FS7: JP22.53, JP23.53
GP110_SPI_2_FS8: JP25.53, JP26.53
GP110_SPI_2_FS9: JP28.53, JP29.53
GP110_SPI_2_FS10: JP31.53, JP32.53
GP110_SPI_2_FS11: JP34.53, JP35.53
GP110_SPI_2_FS12: JP37.53, JP38.53
GP110_SPI_2_FS13: JP40.53, JP41.53
GP110_SPI_2_FS14: JP43.53, JP44.53
GP110_SPI_2_FS15: JP46.53, JP47.53
GP111: JP37.32, JP38.32
GP111_SPI_2_FS1: JP2.51, JP3.51
GP111_SPI_2_FS2: JP4.51, JP5.51
GP111_SPI_2_FS3: JP7.51, JP8.51
GP111_SPI_2_FS4: JP10.51, JP11.51
GP111_SPI_2_FS5: JP13.51, JP14.51
GP111_SPI_2_FS6: JP16.51, JP17.51
GP111_SPI_2_FS7: JP19.51, JP20.51
GP111_SPI_2_FS8: JP22.51, JP23.51
GP111_SPI_2_FS9: JP25.51, JP26.51
GP111_SPI_2_FS10: JP28.51, JP29.51
GP111_SPI_2_FS11: JP31.51, JP32.51
GP111_SPI_2_FS12: JP34.51, JP35.51
GP111_SPI_2_FS13: JP37.51, JP38.51
GP111_SPI_2_FS14: JP40.51, JP41.51
GP111_SPI_2_FS15: JP43.51, JP44.51
GP111_SPI_2_FS16: JP46.51, JP47.51
GP112: JP37.30, JP38.30
GP113: JP37.28, JP38.28
GP114: JP37.26, JP38.26
GP114_SPI_2_RXD: JP2.59, JP3.59
GP114_SPI_2_RXD1: JP4.59, JP5.59
GP114_SPI_2_RXD2: JP7.59, JP8.59
GP114_SPI_2_RXD3: JP10.59, JP11.59
GP114_SPI_2_RXD4: JP13.59, JP14.59
GP114_SPI_2_RXD5: JP16.59, JP17.59
GP114_SPI_2_RXD6: JP19.59, JP20.59
GP114_SPI_2_RXD7: JP22.59, JP23.59
GP114_SPI_2_RXD8: JP25.59, JP26.59
GP114_SPI_2_RXD9: JP28.59, JP29.59
GP114_SPI_2_RXD10: JP31.59, JP32.59
GP114_SPI_2_RXD11: JP34.59, JP35.59
GP114_SPI_2_RXD12: JP37.59, JP38.59
GP114_SPI_2_RXD13: JP40.59, JP41.59
GP114_SPI_2_RXD14: JP43.59, JP44.59
GP114_SPI_2_RXD15: JP46.59, JP47.59
GP115: JP37.25, JP38.25
GP115_SPI_2_TXD: JP2.57, JP3.57
GP115_SPI_2_TXD1: JP4.57, JP5.57
GP115_SPI_2_TXD2: JP7.57, JP8.57
GP115_SPI_2_TXD3: JP10.57, JP11.57
GP115_SPI_2_TXD4: JP13.57, JP14.57
GP115_SPI_2_TXD5: JP16.57, JP17.57
GP115_SPI_2_TXD6: JP19.57, JP20.57
GP115_SPI_2_TXD7: JP22.57, JP23.57
GP115_SPI_2_TXD8: JP25.57, JP26.57
GP115_SPI_2_TXD9: JP28.57, JP29.57
GP115_SPI_2_TXD10: JP31.57, JP32.57
GP115_SPI_2_TXD11: JP34.57, JP35.57
GP115_SPI_2_TXD12: JP37.57, JP38.57
GP115_SPI_2_TXD13: JP40.57, JP41.57
GP115_SPI_2_TXD14: JP43.57, JP44.57
GP115_SPI_2_TXD15: JP46.57, JP47.57
GP116: JP37.24, JP38.24
GP117: JP40.48, JP41.48
GP118: JP40.42, JP41.42
GP119: JP40.34, JP41.34
GP120: JP40.32, JP41.32
GP121: JP40.30, JP41.30
GP122: JP40.28, JP41.28
GP123: JP40.26, JP41.26
GP124: JP40.25, JP41.25
GP125: JP40.24, JP41.24
GP126: JP43.48, JP44.48
GP127: JP43.42, JP44.42
GP128: JP43.34, JP44.34
GP128_UART_1_CTS: JP2.65, JP3.65
GP128_UART_1_CTS1: JP4.65, JP5.65
GP128_UART_1_CTS2: JP7.65, JP8.65
GP128_UART_1_CTS3: JP10.65, JP11.65
GP128_UART_1_CTS4: JP13.65, JP14.65
GP128_UART_1_CTS5: JP16.65, JP17.65
GP128_UART_1_CTS6: JP19.65, JP20.65
GP128_UART_1_CTS7: JP22.65, JP23.65
GP128_UART_1_CTS8: JP25.65, JP26.65
GP128_UART_1_CTS9: JP28.65, JP29.65
GP128_UART_1_CTS10: JP31.65, JP32.65
GP128_UART_1_CTS11: JP34.65, JP35.65
GP128_UART_1_CTS12: JP37.65, JP38.65
GP128_UART_1_CTS13: JP40.65, JP41.65
GP128_UART_1_CTS14: JP43.65, JP44.65
GP128_UART_1_CTS15: JP46.65, JP47.65
GP129: JP43.32, JP44.32
GP129_UART_1_RTS: JP2.63, JP3.63
GP129_UART_1_RTS1: JP4.63, JP5.63
GP129_UART_1_RTS2: JP7.63, JP8.63
GP129_UART_1_RTS3: JP10.63, JP11.63
GP129_UART_1_RTS4: JP13.63, JP14.63
GP129_UART_1_RTS5: JP16.63, JP17.63
GP129_UART_1_RTS6: JP19.63, JP20.63
GP129_UART_1_RTS7: JP22.63, JP23.63
GP129_UART_1_RTS8: JP25.63, JP26.63
GP129_UART_1_RTS9: JP28.63, JP29.63
GP129_UART_1_RTS10: JP31.63, JP32.63
GP129_UART_1_RTS11: JP34.63, JP35.63
GP129_UART_1_RTS12: JP37.63, JP38.63
GP129_UART_1_RTS13: JP40.63, JP41.63
GP129_UART_1_RTS14: JP43.63, JP44.63
GP129_UART_1_RTS15: JP46.63, JP47.63
GP130: JP43.30, JP44.30
GP130_UART_1_RX: JP2.61, JP3.61
GP130_UART_1_RX1: JP4.61, JP5.61
GP130_UART_1_RX2: JP7.61, JP8.61
GP130_UART_1_RX3: JP10.61, JP11.61
GP130_UART_1_RX4: JP13.61, JP14.61
GP130_UART_1_RX5: JP16.61, JP17.61
GP130_UART_1_RX6: JP19.61, JP20.61
GP130_UART_1_RX7: JP22.61, JP23.61
GP130_UART_1_RX8: JP25.61, JP26.61
GP130_UART_1_RX9: JP28.61, JP29.61
GP130_UART_1_RX10: JP31.61, JP32.61
GP130_UART_1_RX11: JP34.61, JP35.61
GP130_UART_1_RX12: JP37.61, JP38.61
GP130_UART_1_RX13: JP40.61, JP41.61
GP130_UART_1_RX14: JP43.61, JP44.61
GP130_UART_1_RX15: JP46.61, JP47.61
GP131: JP43.28, JP44.28
GP131_UART_1_TX: JP2.46, JP3.46
GP131_UART_1_TX1: JP4.46, JP5.46
GP131_UART_1_TX2: JP7.46, JP8.46
GP131_UART_1_TX3: JP10.46, JP11.46
GP131_UART_1_TX4: JP13.46, JP14.46
GP131_UART_1_TX5: JP16.46, JP17.46
GP131_UART_1_TX6: JP19.46, JP20.46
GP131_UART_1_TX7: JP22.46, JP23.46
GP131_UART_1_TX8: JP25.46, JP26.46
GP131_UART_1_TX9: JP28.46, JP29.46
GP131_UART_1_TX10: JP31.46, JP32.46
GP131_UART_1_TX11: JP34.46, JP35.46
GP131_UART_1_TX12: JP37.46, JP38.46
GP131_UART_1_TX13: JP40.46, JP41.46
GP131_UART_1_TX14: JP43.46, JP44.46
GP131_UART_1_TX15: JP46.46, JP47.46
GP132: JP43.26, JP44.26
GP133: JP43.25, JP44.25
GP134: JP43.24, JP44.24
GP134_UART_2_RX: JP2.22, JP3.22
GP134_UART_2_RX1: JP4.22, JP5.22
GP134_UART_2_RX2: JP7.22, JP8.22
GP134_UART_2_RX3: JP10.22, JP11.22
GP134_UART_2_RX4: JP13.22, JP14.22
GP134_UART_2_RX5: JP16.22, JP17.22
GP134_UART_2_RX6: JP19.22, JP20.22
GP134_UART_2_RX7: JP22.22, JP23.22
GP134_UART_2_RX8: JP25.22, JP26.22
GP134_UART_2_RX9: JP28.22, JP29.22
GP134_UART_2_RX10: JP31.22, JP32.22
GP134_UART_2_RX11: JP34.22, JP35.22
GP134_UART_2_RX12: JP37.22, JP38.22
GP134_UART_2_RX13: JP40.22, JP41.22
GP134_UART_2_RX14: JP43.22, JP44.22
GP134_UART_2_RX15: JP46.22, JP47.22
GP135: JP46.48, JP47.48
GP135_UART_2_TX: JP2.27, JP3.27
GP135_UART_2_TX1: JP4.27, JP5.27
GP135_UART_2_TX2: JP7.27, JP8.27
GP135_UART_2_TX3: JP10.27, JP11.27
GP135_UART_2_TX4: JP13.27, JP14.27
GP135_UART_2_TX5: JP16.27, JP17.27
GP135_UART_2_TX6: JP19.27, JP20.27
GP135_UART_2_TX7: JP22.27, JP23.27
GP135_UART_2_TX8: JP25.27, JP26.27
GP135_UART_2_TX9: JP28.27, JP29.27
GP135_UART_2_TX10: JP31.27, JP32.27
GP135_UART_2_TX11: JP34.27, JP35.27
GP135_UART_2_TX12: JP37.27, JP38.27
GP135_UART_2_TX13: JP40.27, JP41.27
GP135_UART_2_TX14: JP43.27, JP44.27
GP135_UART_2_TX15: JP46.27, JP47.27
GP136: JP46.42, JP47.42
GP137: JP46.34, JP47.34
GP138: JP46.32, JP47.32
GP139: JP46.30, JP47.30
GP140: JP46.28, JP47.28
GP141: JP46.26, JP47.26
GP142: JP46.25, JP47.25
GP143: JP46.24, JP47.24
GP165: JP2.25, JP3.25
GP182_PWM1: JP4.37, JP5.37
GP182_PWM2: JP2.37, JP3.37
GP182_PWM3: JP7.37, JP8.37
GP182_PWM4: JP10.37, JP11.37
GP182_PWM5: JP13.37, JP14.37
GP182_PWM6: JP16.37, JP17.37
GP182_PWM7: JP19.37, JP20.37
GP182_PWM8: JP22.37, JP23.37
GP182_PWM9: JP25.37, JP26.37
GP182_PWM10: JP28.37, JP29.37
GP182_PWM11: JP31.37, JP32.37
GP182_PWM12: JP34.37, JP35.37
GP182_PWM13: JP37.37, JP38.37
GP182_PWM14: JP40.37, JP41.37
GP182_PWM15: JP43.37, JP44.37
GP182_PWM16: JP46.37, JP47.37
GP183_PWM1: JP4.39, JP5.39
GP183_PWM2: JP7.39, JP8.39
GP183_PWM3: JP2.39, JP3.39
GP183_PWM4: JP10.39, JP11.39
GP183_PWM5: JP13.39, JP14.39
GP183_PWM6: JP16.39, JP17.39
GP183_PWM7: JP19.39, JP20.39
GP183_PWM8: JP22.39, JP23.39
GP183_PWM9: JP25.39, JP26.39
GP183_PWM10: JP28.39, JP29.39
GP183_PWM11: JP31.39, JP32.39
GP183_PWM12: JP34.39, JP35.39
GP183_PWM13: JP37.39, JP38.39
GP183_PWM14: JP40.39, JP41.39
GP183_PWM15: JP43.39, JP44.39
GP183_PWM16: JP46.39, JP47.39
HV_SCL: R2.1, SJ4.2, U1.10, U2.6
HV_SCL1: R9.1, SJ10.2, U4.10, U5.6
HV_SCL2: R16.1, SJ16.2, U7.10, U8.6
HV_SCL3: R23.1, SJ22.2, U10.10, U11.6
HV_SCL4: R30.1, SJ28.2, U13.10, U14.6
HV_SCL5: R37.1, SJ34.2, U16.10, U17.6
HV_SCL6: R44.1, SJ40.2, U19.10, U20.6
HV_SCL7: R51.1, SJ46.2, U22.10, U23.6
HV_SCL8: R58.1, SJ52.2, U25.10, U26.6
HV_SCL9: R65.1, SJ58.2, U28.10, U29.6
HV_SCL10: R72.1, SJ64.2, U31.10, U32.6
HV_SCL11: R79.1, SJ70.2, U34.10, U35.6
HV_SCL12: R86.1, SJ76.2, U37.10, U38.6
HV_SCL13: R93.1, SJ82.2, U40.10, U41.6
HV_SCL14: R100.1, SJ88.2, U43.10, U44.6
HV_SCL15: R107.1, SJ94.2, U46.10, U47.6
HV_SDA: R1.1, SJ3.2, U1.9, U2.5
HV_SDA1: R8.1, SJ9.2, U4.9, U5.5
HV_SDA2: R15.1, SJ15.2, U7.9, U8.5
HV_SDA3: R22.1, SJ21.2, U10.9, U11.5
HV_SDA4: R29.1, SJ27.2, U13.9, U14.5
HV_SDA5: R36.1, SJ33.2, U16.9, U17.5
HV_SDA6: R43.1, SJ39.2, U19.9, U20.5
HV_SDA7: R50.1, SJ45.2, U22.9, U23.5
HV_SDA8: R57.1, SJ51.2, U25.9, U26.5
HV_SDA9: R64.1, SJ57.2, U28.9, U29.5
HV_SDA10: R71.1, SJ63.2, U31.9, U32.5
HV_SDA11: R78.1, SJ69.2, U34.9, U35.5
HV_SDA12: R85.1, SJ75.2, U37.9, U38.5
HV_SDA13: R92.1, SJ81.2, U40.9, U41.5
HV_SDA14: R99.1, SJ87.2, U43.9, U44.5
HV_SDA15: R106.1, SJ93.2, U46.9, U47.5
MSIC_SLP_CLK: JP2.7, JP3.7
MSIC_SLP_CLK1: JP4.7, JP5.7
MSIC_SLP_CLK2: JP7.7, JP8.7
MSIC_SLP_CLK3: JP10.7, JP11.7
MSIC_SLP_CLK4: JP13.7, JP14.7
MSIC_SLP_CLK5: JP16.7, JP17.7
MSIC_SLP_CLK6: JP19.7, JP20.7
MSIC_SLP_CLK7: JP22.7, JP23.7
MSIC_SLP_CLK8: JP25.7, JP26.7
MSIC_SLP_CLK9: JP28.7, JP29.7
MSIC_SLP_CLK10: JP31.7, JP32.7
MSIC_SLP_CLK11: JP34.7, JP35.7
MSIC_SLP_CLK12: JP37.7, JP38.7
MSIC_SLP_CLK13: JP40.7, JP41.7
MSIC_SLP_CLK14: JP43.7, JP44.7
MSIC_SLP_CLK15: JP46.7, JP47.7
unnamed: R3.1, U2.7, U2.8
unnamed: R4.1, SJ6.2, U2.2
unnamed: R6.2, SJ1.2
unnamed: R5.1, SJ5.2, U2.3
unnamed: C5.1, R7.1
unnamed: R10.1, U5.7, U5.8
unnamed: R13.2, SJ7.2
unnamed: R11.1, SJ12.2, U5.2
unnamed: R12.1, SJ11.2, U5.3
unnamed: C10.1, R14.1
unnamed: R17.1, U8.7, U8.8
unnamed: R20.2, SJ13.2
unnamed: R18.1, SJ18.2, U8.2
unnamed: R19.1, SJ17.2, U8.3
unnamed: C15.1, R21.1
unnamed: R24.1, U11.7, U11.8
unnamed: R27.2, SJ19.2
unnamed: R25.1, SJ24.2, U11.2
unnamed: R26.1, SJ23.2, U11.3
unnamed: C20.1, R28.1
unnamed: R31.1, U14.7, U14.8
unnamed: R34.2, SJ25.2
unnamed: R32.1, SJ30.2, U14.2
unnamed: R33.1, SJ29.2, U14.3
unnamed: C25.1, R35.1
unnamed: R38.1, U17.7, U17.8
unnamed: R41.2, SJ31.2
unnamed: R39.1, SJ36.2, U17.2
unnamed: R40.1, SJ35.2, U17.3
unnamed: C30.1, R42.1
unnamed: R45.1, U20.7, U20.8
unnamed: R48.2, SJ37.2
unnamed: R46.1, SJ42.2, U20.2
unnamed: R47.1, SJ41.2, U20.3
unnamed: C35.1, R49.1
unnamed: R52.1, U23.7, U23.8
unnamed: R55.2, SJ43.2
unnamed: R53.1, SJ48.2, U23.2
unnamed: R54.1, SJ47.2, U23.3
unnamed: C40.1, R56.1
unnamed: R59.1, U26.7, U26.8
unnamed: R62.2, SJ49.2
unnamed: R60.1, SJ54.2, U26.2
unnamed: R61.1, SJ53.2, U26.3
unnamed: C45.1, R63.1
unnamed: R66.1, U29.7, U29.8
unnamed: R69.2, SJ55.2
unnamed: R67.1, SJ60.2, U29.2
unnamed: R68.1, SJ59.2, U29.3
unnamed: C50.1, R70.1
unnamed: R73.1, U32.7, U32.8
unnamed: R76.2, SJ61.2
unnamed: R74.1, SJ66.2, U32.2
unnamed: R75.1, SJ65.2, U32.3
unnamed: C55.1, R77.1
unnamed: R80.1, U35.7, U35.8
unnamed: R83.2, SJ67.2
unnamed: R81.1, SJ72.2, U35.2
unnamed: R82.1, SJ71.2, U35.3
unnamed: C60.1, R84.1
unnamed: R87.1, U38.7, U38.8
unnamed: R90.2, SJ73.2
unnamed: R88.1, SJ78.2, U38.2
unnamed: R89.1, SJ77.2, U38.3
unnamed: C65.1, R91.1
unnamed: R94.1, U41.7, U41.8
unnamed: R97.2, SJ79.2
unnamed: R95.1, SJ84.2, U41.2
unnamed: R96.1, SJ83.2, U41.3
unnamed: C70.1, R98.1
unnamed: R101.1, U44.7, U44.8
unnamed: R104.2, SJ85.2
unnamed: R102.1, SJ90.2, U44.2
unnamed: R103.1, SJ89.2, U44.3
unnamed: C75.1, R105.1
unnamed: R108.1, U47.7, U47.8
unnamed: R111.2, SJ91.2
unnamed: R109.1, SJ96.2, U47.2
unnamed: R110.1, SJ95.2, U47.3
unnamed: C80.1, R112.1
OSC_CLK_OUT: JP2.67, JP3.67
OSC_CLK_OUT1: JP4.67, JP5.67
OSC_CLK_OUT2: JP7.67, JP8.67
OSC_CLK_OUT3: JP10.67, JP11.67
OSC_CLK_OUT4: JP13.67, JP14.67
OSC_CLK_OUT5: JP16.67, JP17.67
OSC_CLK_OUT6: JP19.67, JP20.67
OSC_CLK_OUT7: JP22.67, JP23.67
OSC_CLK_OUT8: JP25.67, JP26.67
OSC_CLK_OUT9: JP28.67, JP29.67
OSC_CLK_OUT10: JP31.67, JP32.67
OSC_CLK_OUT11: JP34.67, JP35.67
OSC_CLK_OUT12: JP37.67, JP38.67
OSC_CLK_OUT13: JP40.67, JP41.67
OSC_CLK_OUT14: JP43.67, JP44.67
OSC_CLK_OUT15: JP46.67, JP47.67
PSW: JP2.21, JP3.21
PSW1: JP4.21, JP5.21
PSW2: JP7.21, JP8.21
PSW3: JP10.21, JP11.21
PSW4: JP13.21, JP14.21
PSW5: JP16.21, JP17.21
PSW6: JP19.21, JP20.21
PSW7: JP22.21, JP23.21
PSW8: JP25.21, JP26.21
PSW9: JP28.21, JP29.21
PSW10: JP31.21, JP32.21
PSW11: JP34.21, JP35.21
PSW12: JP37.21, JP38.21
PSW13: JP40.21, JP41.21
PSW14: JP43.21, JP44.21
PSW15: JP46.21, JP47.21
PWRBTN#: JP2.17, JP3.17
PWRBTN#1: JP4.17, JP5.17
PWRBTN#2: JP7.17, JP8.17
PWRBTN#3: JP10.17, JP11.17
PWRBTN#4: JP13.17, JP14.17
PWRBTN#5: JP16.17, JP17.17
PWRBTN#6: JP19.17, JP20.17
PWRBTN#7: JP22.17, JP23.17
PWRBTN#8: JP25.17, JP26.17
PWRBTN#9: JP28.17, JP29.17
PWRBTN#10: JP31.17, JP32.17
PWRBTN#11: JP34.17, JP35.17
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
